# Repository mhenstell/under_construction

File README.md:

# under_construction
Repository for the 2018 BM Project 'Under Construction'

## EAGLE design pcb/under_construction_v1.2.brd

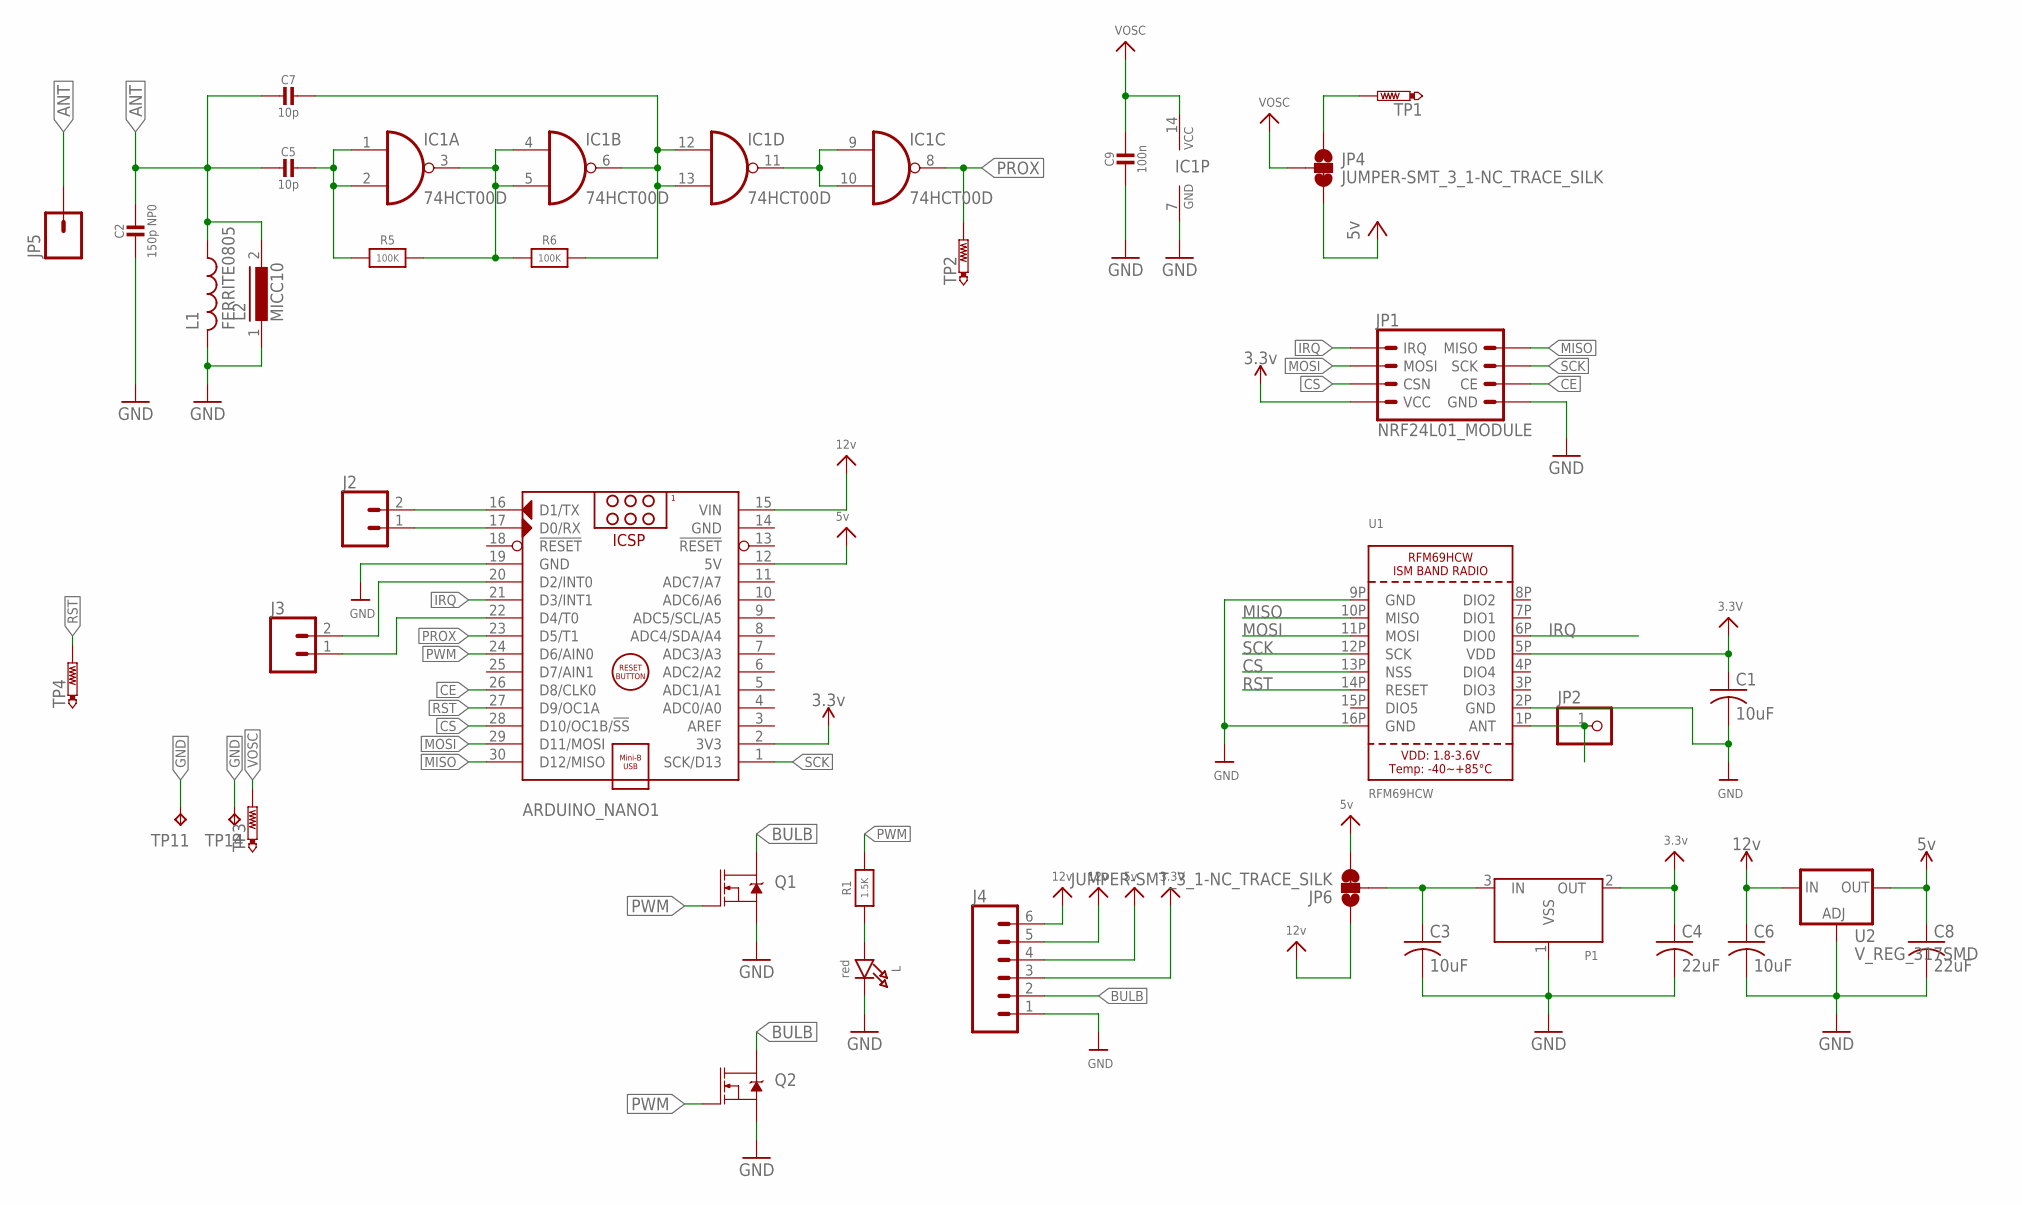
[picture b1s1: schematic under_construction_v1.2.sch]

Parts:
ARDUINO_NANO1: ARDUINO_NANO
C1: 10uF; C0805; PARTNO EMK212ABJ106MG-T
C2: 150p NP0; 0805-NO; PARTNO C0805C151J5GACTU
C3, C6: 10uF; C0805; PARTNO LMK212AB7106MG-T
C4, C8: 22uF; C0805; PARTNO CL21A226MQQNNNE
C5, C7: 10p; 0805-NO; PARTNO CL21C100DBANNNC
C9: 100n; 0805-NO; PARTNO 885012207072
IC1: 74HCT00D; SO14; PARTNO SN74HC00NSR
J2, J3: CONN_02PTH3; 1X02_LONGPADS
J4: CONN_06LONGPADS; 1X06_LONGPADS
JP1: NRF24L01_MODULE; 2X4
JP2: HEADER-1X1ROUND; 1X01_ROUND
JP4, JP6: JUMPER-SMT_3_1-NC_TRACE_SILK; SMT-JUMPER_3_1-NC_TRACE_SILK
JP5: M01PTH; 1X01
L: red; CHIPLED_0603_NOOUTLINE; PARTNO 150080SS75000
L1: FERRITE0805; 0805; PARTNO MLZ2012N100LT000
L2: MICC10; PARTNO B78108T1103K000
P1: XC6206SOT-89; SOT-89; PARTNO AZ1117CR-3.3TRG1
Q1, Q2: MOSFET-NCH-FQP30N06L; TO220V; PARTNO IRF3708PBF
R1: 1.5K; 0603-NO; PARTNO RNCP0603FTD1K50
R5, R6: 100K; 0805-NO; PARTNO RC2012J104CS
TP1, TP3, TP4: VOSC; TP15R
TP2: PROX; TP15R
TP11, TP14: VOSC; TP15SQ
U1: RFM69HCW; RFMHCW_SMT
U2: V_REG_317SMD; SOT223; PARTNO AZ1117IH-5.0TRG1

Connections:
3.3V: ARDUINO_NANO1.2 (3V3), C1.1, C4.1, J4.3, JP1.7 (VCC), P1.2 (OUT), U1.5P (VDD)
5V: ARDUINO_NANO1.12 (5V), C8.1, J4.4, JP4.3, JP6.3, U2.2 (OUT)
12V: ARDUINO_NANO1.15 (VIN), C6.1, J4.5, J4.6, JP6.1, U2.3 (IN)
ANT: C2.1, C5.2, C7.2, JP5.1, L1.1, L2.2
BULB: J4.2, Q1.2 (D), Q2.2 (D)
CE: ARDUINO_NANO1.26 (D8/CLK0), JP1.6 (CE)
CS: ARDUINO_NANO1.28 (D10/OC1B/!SS), JP1.5 (CSN), U1.13P (NSS)
GND: ARDUINO_NANO1.14 (GND), ARDUINO_NANO1.19 (GND), C1.2, C2.2, C3.2, C4.2, C6.2, C8.2, C9.2, IC1.7 (GND), J4.1, JP1.8 (GND), L.C, L1.2, L2.1, P1.1 (VSS), Q1.3 (S), Q2.3 (S), TP11.TP, TP14.TP, U1.2P (GND), U1.9P (GND), U1.16P (GND), U2.1 (ADJ)
IRQ: ARDUINO_NANO1.21 (D3/INT1), JP1.1 (IRQ), U1.6P (DIO0)
MISO: ARDUINO_NANO1.30 (D12/MISO), JP1.2 (MISO), U1.10P (MISO)
MOSI: ARDUINO_NANO1.29 (D11/MOSI), JP1.3 (MOSI), U1.11P (MOSI)
unnamed: JP2.1, U1.1P (ANT)
unnamed: C5.1, IC1.1 (I0), IC1.2 (I1), R5.1
unnamed: IC1.3 (O), IC1.4 (I0), IC1.5 (I1), R5.2, R6.1
unnamed: C7.1, IC1.6 (O), IC1.12 (I0), IC1.13 (I1), R6.2
unnamed: C3.1, JP6.2, P1.3 (IN)
unnamed: ARDUINO_NANO1.17 (D0/RX), J2.1
unnamed: IC1.9 (I0), IC1.10 (I1), IC1.11 (O)
unnamed: ARDUINO_NANO1.16 (D1/TX), J2.2
unnamed: ARDUINO_NANO1.20 (D2/INT0), J3.2
unnamed: JP4.1, TP1.TP
unnamed: ARDUINO_NANO1.22 (D4/T0), J3.1
unnamed: L.A, R1.1
PROX: ARDUINO_NANO1.23 (D5/T1), IC1.8 (O), TP2.TP
PWM: ARDUINO_NANO1.24 (D6/AIN0), Q1.1 (G), Q2.1 (G), R1.2
RST: ARDUINO_NANO1.27 (D9/OC1A), TP4.TP, U1.14P (RESET)
SCK: ARDUINO_NANO1.1 (SCK/D13), JP1.4 (SCK), U1.12P (SCK)
VOSC: C9.1, IC1.14 (VCC), JP4.2, TP3.TP

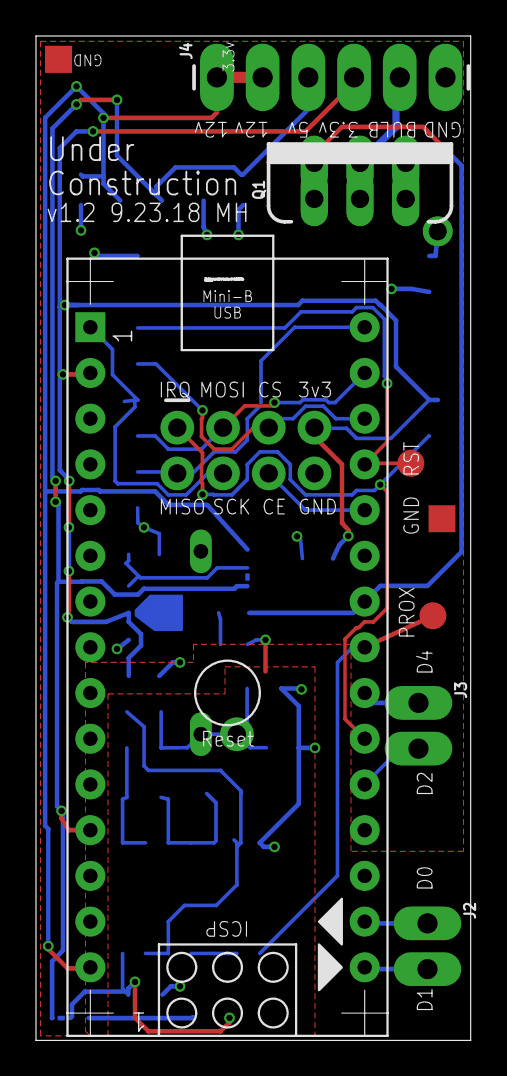
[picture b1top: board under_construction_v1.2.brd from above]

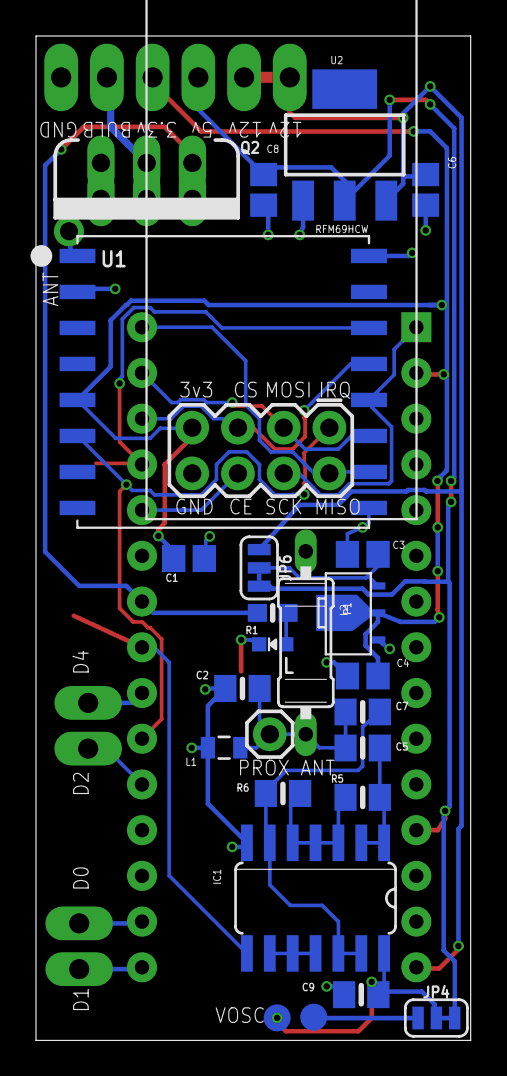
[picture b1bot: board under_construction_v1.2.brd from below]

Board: 2 copper layers, 24.1 x 55.8 mm, 36 parts (26 on the bottom side), 28 nets.

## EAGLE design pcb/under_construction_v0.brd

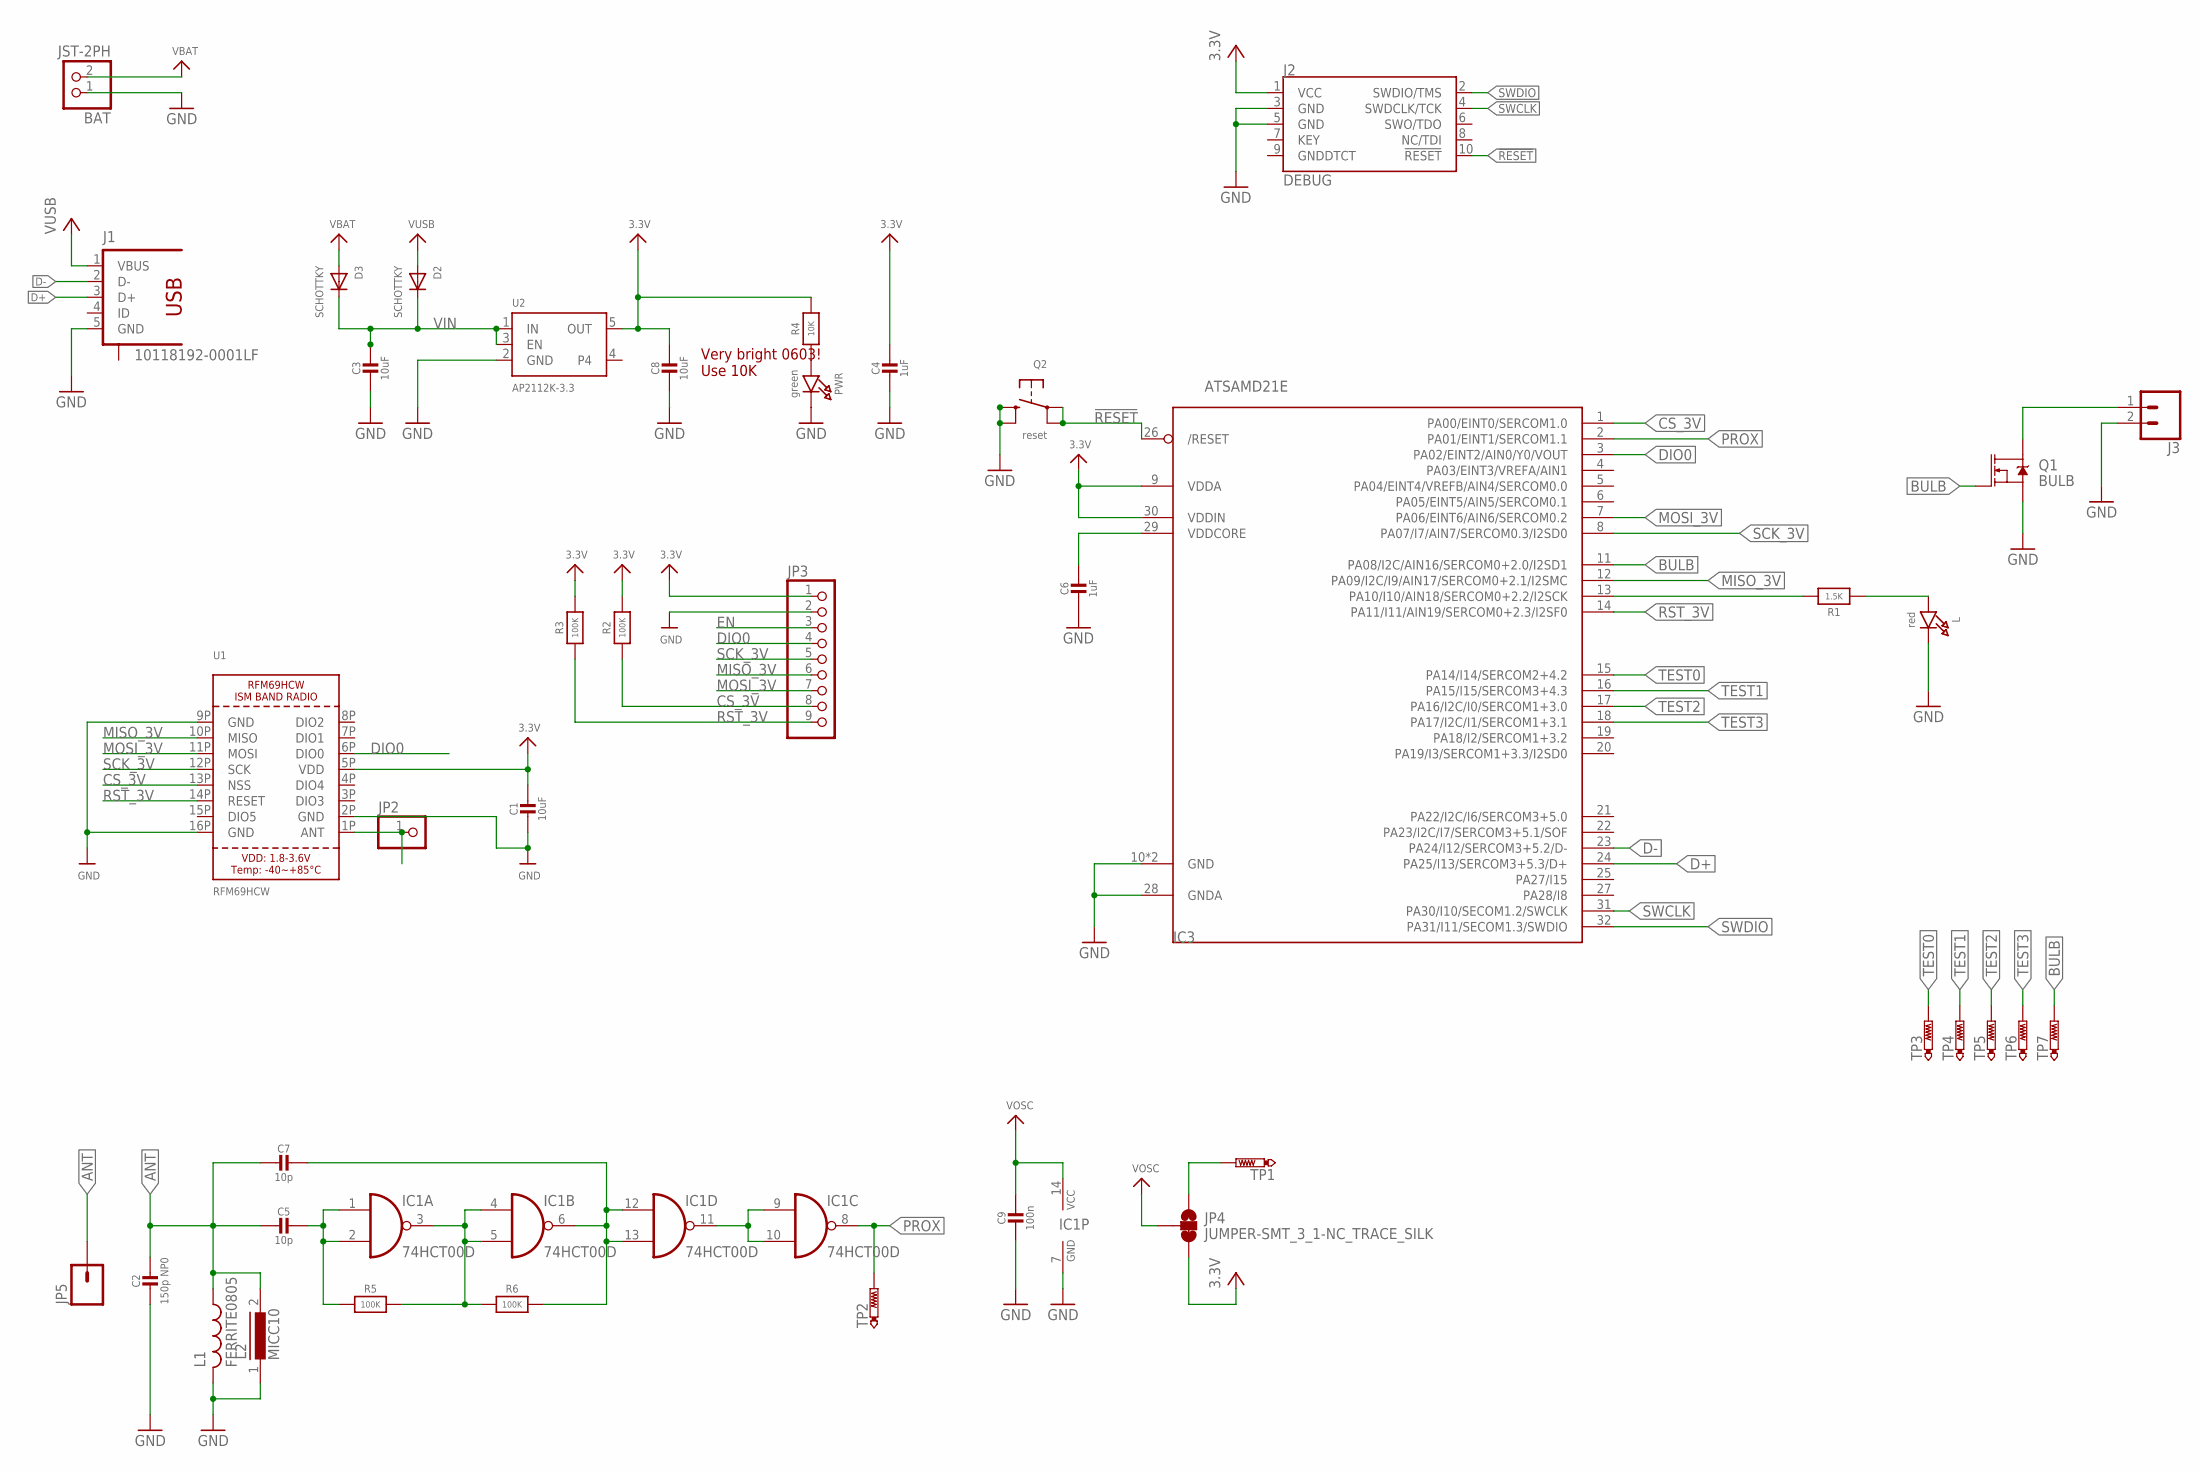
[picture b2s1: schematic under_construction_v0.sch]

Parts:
BAT: JST-2PH; JSTPH2; PARTNO S2B-PH-SM4-TB(LF)(SN)
C1, C3, C8: 10uF; 0805-NO; PARTNO GRM21BR71A106MA73L
C2: 150p NP0; 0805-NO; PARTNO C0805C151J5GACTU
C4, C6: 1uF; 0603-NO; PARTNO CL21B105KOFNNNE
C5, C7: 10p; 0805-NO; PARTNO CL21C100JCANNNC
C9: 100n; 0805-NO; PARTNO C0805C104K5RACTU
D2, D3: SCHOTTKY; SOD-123FL; PARTNO B130LAW-7-F
IC1: 74HCT00D; SO14; PARTNO SN74HC00NSR
IC3: ATSAMD21E; QFN32_5MM; PARTNO ATSAMD21E18A-MU
J1: 10118192-0001LF; PARTNO 10118192-0001LF
J2: DEBUG; SAMTECH_FTSH-105-01; PARTNO 3220-10-0300-00
J3: CONN_02; 1X02
JP2: HEADER-1X1ROUND; 1X01_ROUND
JP3: HEADER-1X970MIL; 1X09_ROUND_70
JP4: JUMPER-SMT_3_1-NC_TRACE_SILK; SMT-JUMPER_3_1-NC_TRACE_SILK
JP5: M01PTH; 1X01
L: red; CHIPLED_0603_NOOUTLINE
L1: FERRITE0805; 0805; PARTNO MLZ2012N100LT000
L2: MICC10; PARTNO B78108T1103K000
PWR: green; CHIPLED_0603_NOOUTLINE
Q1: BULB; SOT323; PARTNO DMG1012UW-7
Q2: reset; BTN_KMR2_4.6X2.8; PARTNO KMR442G ULC LFS
R1: 1.5K; 0603-NO; PARTNO RNCP0603FTD1K50
R2, R3, R5, R6: 100K; 0805-NO; PARTNO RC2012J104CS
R4: 10K; 0603-NO
TP1: VOSC; TP15R
TP2: PROX; TP15R
TP3, TP4, TP5, TP6, TP7: PTR1TP10R; TP10R
U1: RFM69HCW; RFMHCW_SMT
U2: AP2112K-3.3; SOT23-5; PARTNO AP2112K-3.3TRG1

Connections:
3.3V: C1.1, C4.1, C8.1, IC3.9 (VDDA), IC3.30 (VDDIN), J2.1 (VCC), JP3.1, JP4.3, R2.2, R3.2, R4.2, U1.5P (VDD), U2.5 (OUT)
!RESET: IC3.26 (/RESET), J2.10 (!RESET), Q2.A, Q2.A' (P1)
ANT: C2.1, C5.2, C7.2, JP5.1, L1.1, L2.2
BULB: IC3.11 (PA08/I2C/AIN16/SERCOM0+2.0/I2SD1), Q1.1 (G), TP7.TP
CS_3V: IC3.1 (PA00/EINT0/SERCOM1.0), JP3.8, R2.1, U1.13P (NSS)
D+: IC3.24 (PA25/I13/SERCOM3+5.3/D+), J1.3 (D+)
D-: IC3.23 (PA24/I12/SERCOM3+5.2/D-), J1.2 (D-)
DIO0: IC3.3 (PA02/EINT2/AIN0/Y0/VOUT), JP3.4, U1.6P (DIO0)
EN: JP3.3
GND: BAT.1, C1.2, C2.2, C3.2, C4.2, C6.2, C8.2, C9.2, IC1.7 (GND), IC3.10 (GND), IC3.28 (GNDA), IC3.33 (GND), J1.5 (GND), J2.3 (GND), J2.5 (GND), J3.2, JP3.2, L.C, L1.2, L2.1, PWR.C, Q1.2 (S), Q2.B (S), Q2.B' (S1), U1.2P (GND), U1.9P (GND), U1.16P (GND), U2.2 (GND)
MISO_3V: IC3.12 (PA09/I2C/I9/AIN17/SERCOM0+2.1/I2SMC), JP3.6, U1.10P (MISO)
MOSI_3V: IC3.7 (PA06/EINT6/AIN6/SERCOM0.2), JP3.7, U1.11P (MOSI)
unnamed: JP2.1, U1.1P (ANT)
unnamed: C5.1, IC1.1 (I0), IC1.2 (I1), R5.1
unnamed: IC1.3 (O), IC1.4 (I0), IC1.5 (I1), R5.2, R6.1
unnamed: C7.1, IC1.6 (O), IC1.12 (I0), IC1.13 (I1), R6.2
unnamed: L.A, R1.1
unnamed: PWR.A, R4.1
unnamed: IC1.9 (I0), IC1.10 (I1), IC1.11 (O)
unnamed: IC3.13 (PA10/I10/AIN18/SERCOM0+2.2/I2SCK), R1.2
unnamed: J3.1, Q1.3 (D)
unnamed: JP4.1, TP1.TP
PROX: IC1.8 (O), IC3.2 (PA01/EINT1/SERCOM1.1), TP2.TP
RST_3V: IC3.14 (PA11/I11/AIN19/SERCOM0+2.3/I2SF0), JP3.9, R3.1, U1.14P (RESET)
SCK_3V: IC3.8 (PA07/I7/AIN7/SERCOM0.3/I2SD0), JP3.5, U1.12P (SCK)
SWCLK: IC3.31 (PA30/I10/SECOM1.2/SWCLK), J2.4 (SWDCLK/TCK)
SWDIO: IC3.32 (PA31/I11/SECOM1.3/SWDIO), J2.2 (SWDIO/TMS)
TEST0: IC3.15 (PA14/I14/SERCOM2+4.2), TP3.TP
TEST1: IC3.16 (PA15/I15/SERCOM3+4.3), TP4.TP
TEST2: IC3.17 (PA16/I2C/I0/SERCOM1+3.0), TP5.TP
TEST3: IC3.18 (PA17/I2C/I1/SERCOM1+3.1), TP6.TP
VBAT: BAT.2, D3.A
VDDCORE1: C6.1, IC3.29 (VDDCORE)
VIN: C3.1, D2.C, D3.C, U2.1 (IN), U2.3 (EN)
VOSC: C9.1, IC1.14 (VCC), JP4.2
VUSB: D2.A, J1.1 (VBUS)

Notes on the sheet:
Very bright 0603! Use 10K

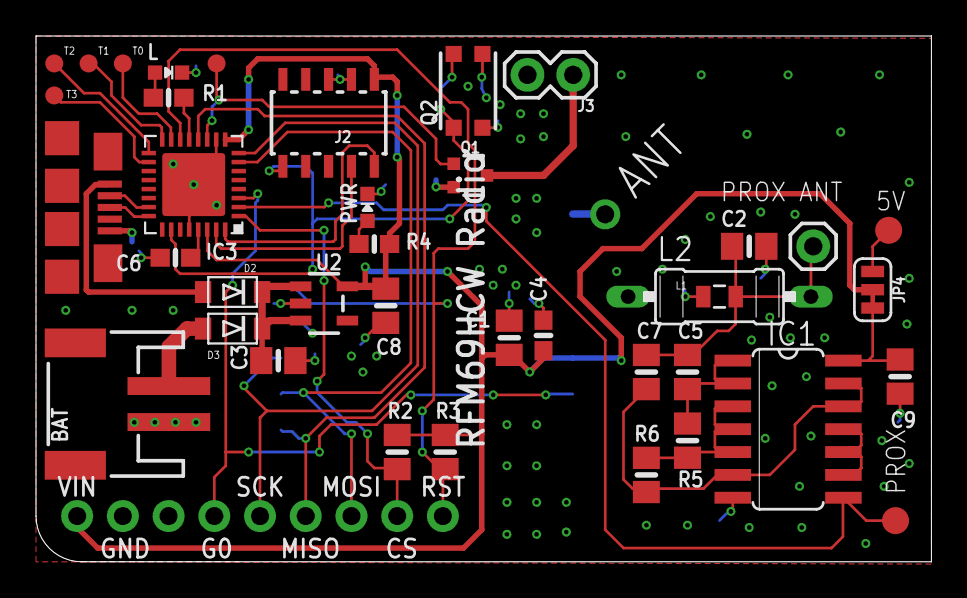
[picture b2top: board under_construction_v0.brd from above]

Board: 2 copper layers, 49.7 x 29.2 mm, 42 parts (1 on the bottom side), 35 nets.

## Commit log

2018-01-31 init
2018-09-10 Adding v1 pcb
2018-09-13 Working redis/serial backend and simulator
2018-09-13 UC library and first DK order
2018-09-13 Cleanup
2018-09-17 PCB V1.1
2018-09-19 Checkin before changing to RSR
2018-09-23 Adding arduino code
2018-09-24 Updating board to v1.2
2018-09-28 Mostly working code with more patterns
2018-09-28 Latest server and light code - now using NRFs
2018-09-28 Updated simulator code, now with ALL_LEVELS support
2018-10-02 Add a project requirements.txt and a python gitignore
2018-10-02 Add problem with blinking light patterns
2018-10-08 Added more effects, mode changing, config reloading
2018-10-08 Added feedback, config to simulator
2018-10-08 Adding cloud chaser version
2018-10-11 Adding watchdog, light on timeout
2018-10-11 Tweaks, bug fixes to python
2018-10-11 Adding pi config
2018-10-11 Adding redis host value

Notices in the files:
parts and their libraries:
microbuilder: This work is placed in the public domain, and may be freely used for commercial and non-commercial work with the following conditions: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
SparkFun-Connectors: Licensing: Creative Commons ShareAlike 4.0 International - https://creativecommons.org/licenses/by-sa/4.0
